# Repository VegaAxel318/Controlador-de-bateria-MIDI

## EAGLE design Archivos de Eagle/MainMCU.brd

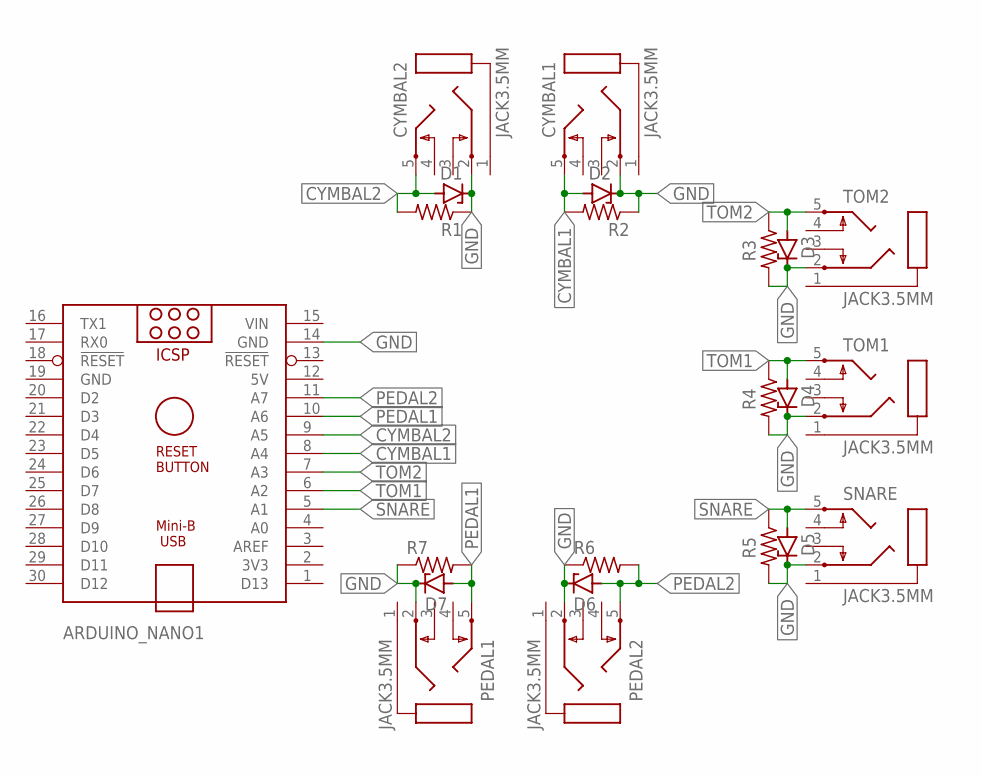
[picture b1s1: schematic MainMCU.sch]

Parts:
ARDUINO_NANO1: ARDUINO_NANO
CYMBAL1, CYMBAL2: JACK3.5MM; PG203J
D1, D2, D3, D4, D5, D6, D7: ZENER-DIODEDO34-7; DO34Z7
PEDAL1, PEDAL2: JACK3.5MM; PG203J
R1, R2, R3, R4, R5, R6, R7: R-US_0207/10; 0207/10
SNARE: JACK3.5MM; PG203J
TOM1, TOM2: JACK3.5MM; PG203J

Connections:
5V: ARDUINO_NANO1.12 (5V)
CYMBAL1: ARDUINO_NANO1.8 (A4), CYMBAL1.5, D2.A, R2.2
CYMBAL2: ARDUINO_NANO1.9 (A5), CYMBAL2.5, D1.A, R1.2
GND: ARDUINO_NANO1.14 (GND), ARDUINO_NANO1.19 (GND), CYMBAL1.2, CYMBAL2.2, D1.C, D2.C, D3.C, D4.C, D5.C, D6.C, D7.C, PEDAL1.2, PEDAL2.2, R1.1, R2.1, R3.2, R4.2, R5.2, R6.1, R7.1, SNARE.2, TOM1.2, TOM2.2
PEDAL1: ARDUINO_NANO1.10 (A6), D7.A, PEDAL1.5, R7.2
PEDAL2: ARDUINO_NANO1.11 (A7), D6.A, PEDAL2.5, R6.2
SNARE: ARDUINO_NANO1.5 (A1), D5.A, R5.1, SNARE.5
TOM1: ARDUINO_NANO1.6 (A2), D4.A, R4.1, TOM1.5
TOM2: ARDUINO_NANO1.7 (A3), D3.A, R3.1, TOM2.5
VIN: ARDUINO_NANO1.15 (VIN)

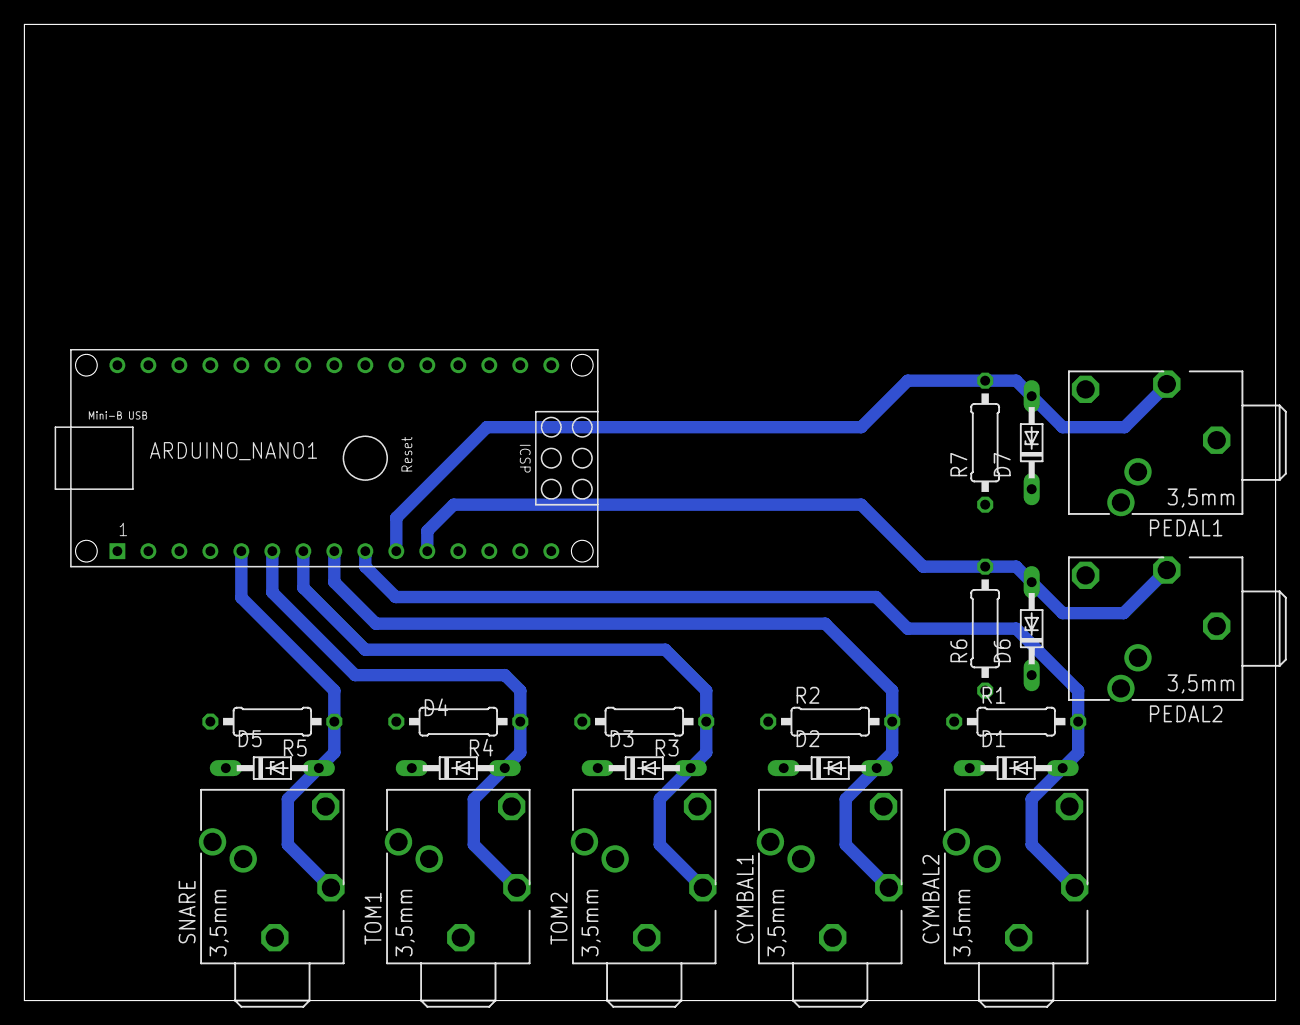
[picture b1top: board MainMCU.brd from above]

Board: 2 copper layers, 102.5 x 80.0 mm, 22 parts (0 on the bottom side), 8 nets.

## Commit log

2024-11-20 Creación del repositorio
    Archivos de código, planos y esquemáticos.
